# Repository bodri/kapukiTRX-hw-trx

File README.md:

# Redundant RC transmitter module & 8 channel receiver
RC Receiver and transmitter module using redundant SX1280 RF modules.

The [firmware](https://github.com/bodri/kapukiTRX-fw-trx) is still under development, but you can take a look already...

[Please take a look at my previous project here](https://github.com/bodri/RcReceiver)

# Design

# Manufacturing
I would like to compare services from [OSHPark](http://oshpark.com)/[OSH Stencils](https://www.oshstencils.com) and [JLCPCB](http://jlcpcb.com), so I ordered:

| Manufacturer | Items             | Price  | Order date | Shipped      | Received   | Total days |
|--------------|-------------------|--------|------------|--------------|------------|------------|
| OSHPark      | 3 PCBs            | $19.80 | 09/11/2019 | 21/11/2019** | 17/12/2019 | 21 (35)**  |
| OSH Stencils | 1 stencil         | $21.60 | 09/11/2019 | 12/11/2019   | 19/11/2019 | 10         |
| JLCPCB       | 10 PCBs + stencil | $28.33 | 09/11/2019 | 14/11/2019   | 03/12/2019 | 21         |

<sub>** Originally was shipped on 21/11/2019 and received on the same day as the JLCPCB package, but I have received a message that the PCBs have "Severe over-etching in some regions" therefore not to use them. OSHPark refabricated them and I received the second batch on 17/12/2019.<sub>

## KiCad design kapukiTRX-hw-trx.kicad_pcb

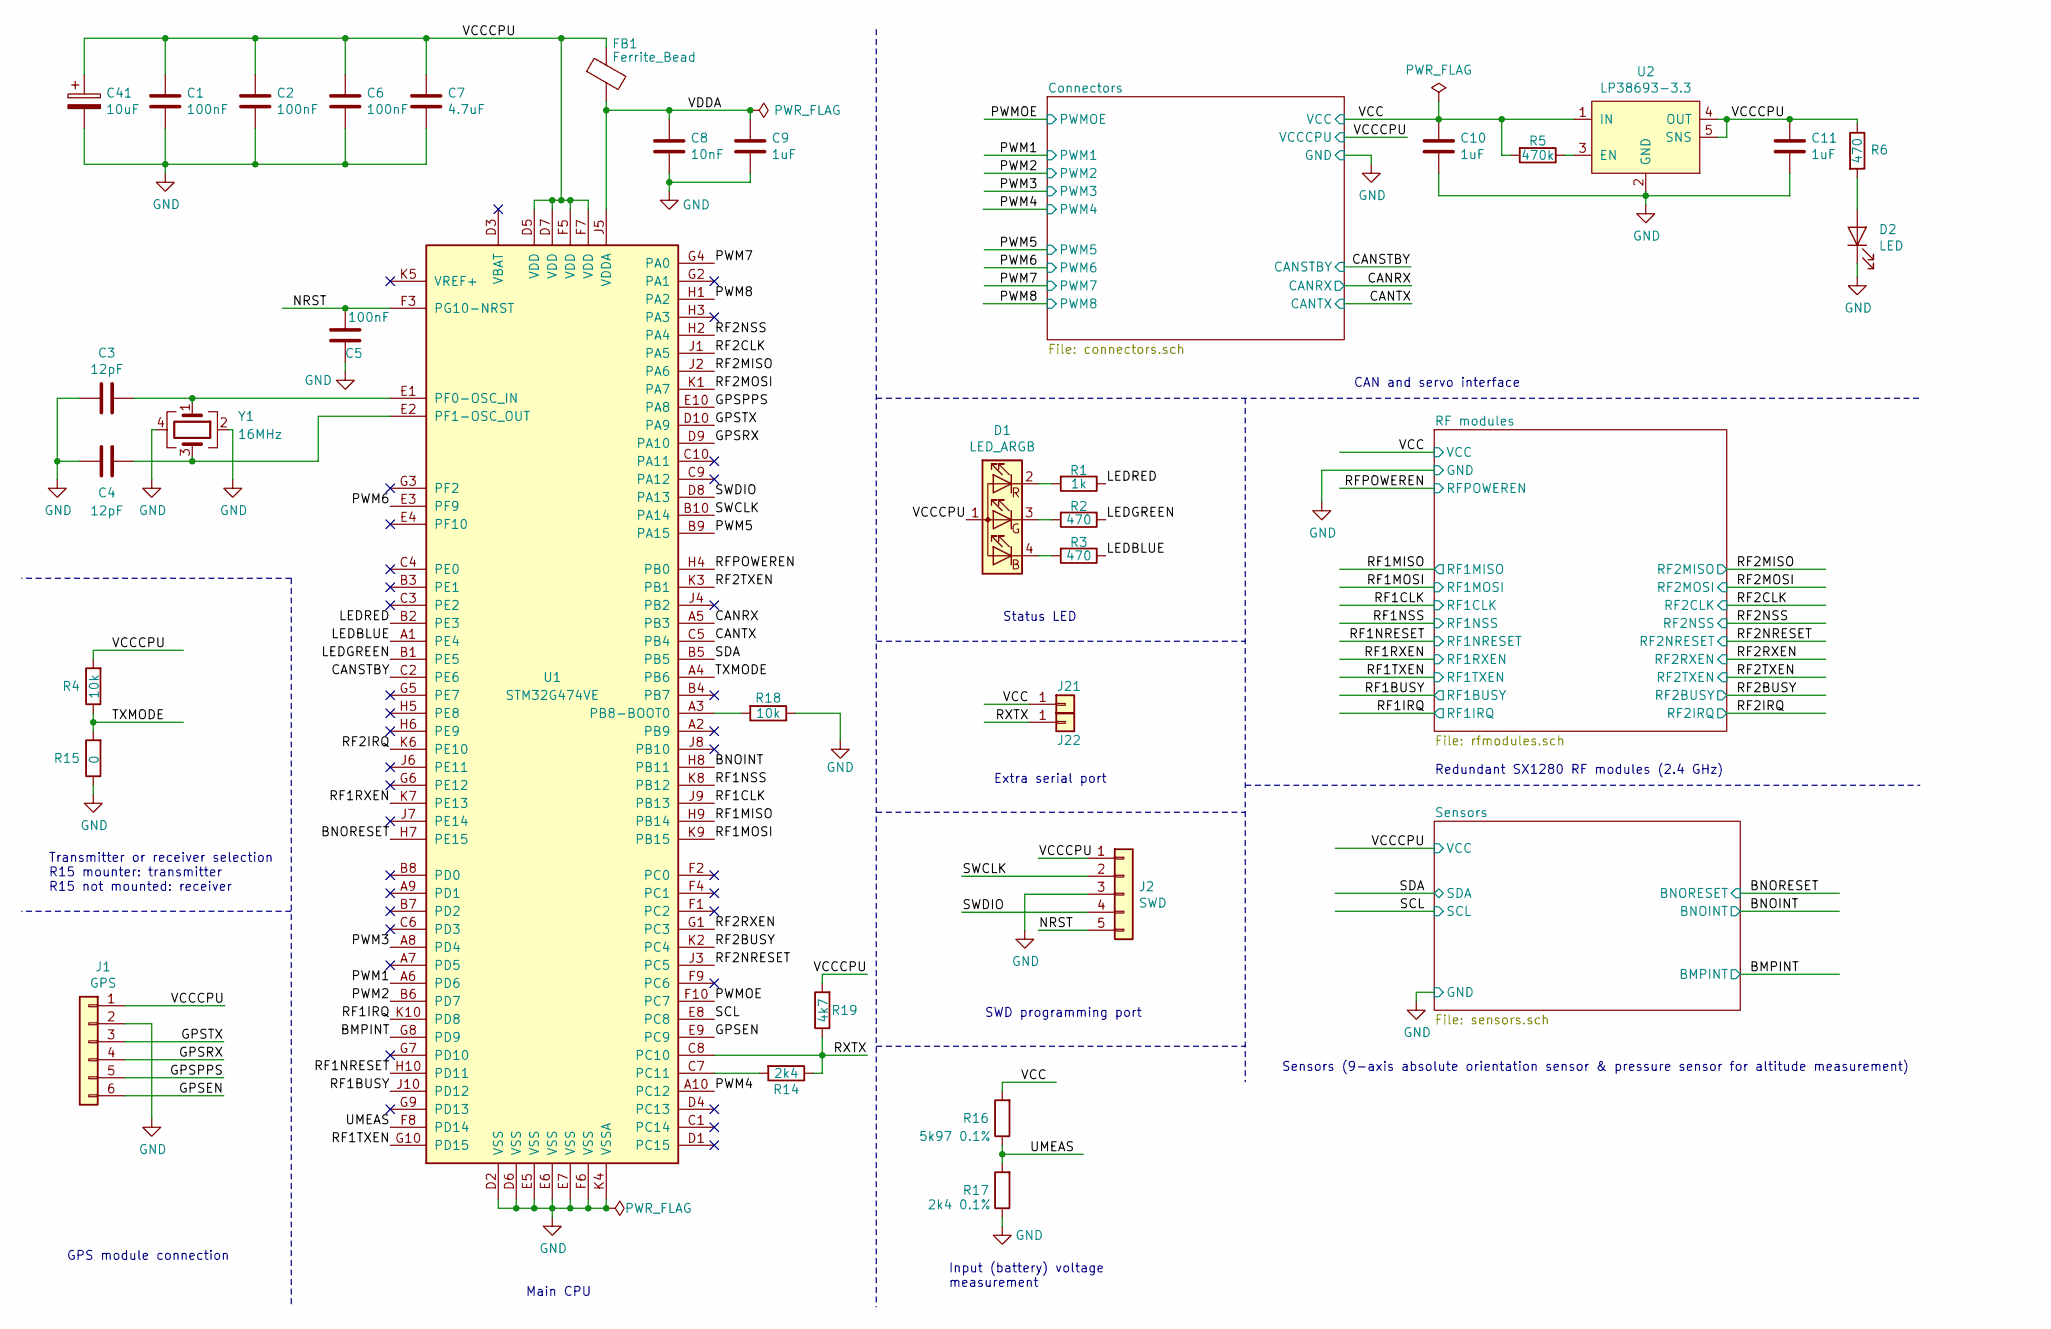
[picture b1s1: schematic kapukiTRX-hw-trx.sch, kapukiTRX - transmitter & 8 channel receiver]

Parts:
C1, C2, C5, C6: 100nF; C_0402_1005Metric
C3, C4: 12pF; C_0402_1005Metric
C7: 4.7uF; C_0402_1005Metric
C8: 10nF; C_0402_1005Metric
C9, C10, C11: 1uF; C_0402_1005Metric
C41: 10uF; CP_EIA-3216-18_Kemet-A
D1: LED_ARGB; LED_Lumex-LX0404
D2: LED; LED_0402_1005Metric
FB1: Ferrite_Bead; L_0402_1005Metric
J1: GPS; JST_SH_BM06B-SRSS-TB_1x06-1MP_P1.00mm_Vertical
J2: SWD; JST_SH_BM05B-SRSS-TB_1x05-1MP_P1.00mm_Vertical
J21, J22: Conn_01x01; PinHeader_1x01_P1.27mm
R1: 1k; R_0402_1005Metric
R2, R3, R6: 470; R_0402_1005Metric
R4, R18: 10k; R_0402_1005Metric
R5: 470k; R_0402_1005Metric
R14: 2k4; R_0402_1005Metric
R15: 0; R_0402_1005Metric
R16: 5k97 0.1%; R_0402_1005Metric
R17: 2k4 0.1%; R_0402_1005Metric
R19: 4k7; R_0402_1005Metric
U1: STM32G474VE; TFBGA-100_10x10_8.0x8.0mm
U2: LP38693-3.3; WSON-6_3x3mm_Pitch0.95mm
Y1: 16MHz; Oscillator_SMD_SeikoEpson_SG210-4Pin_2.5x2.0mm

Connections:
/BMPINT: U1.G8 (PD9); also elsewhere on the board
/BNOINT: U1.H8 (PB11); also elsewhere on the board
/BNORESET: U1.H7 (PE15); also elsewhere on the board
/CANRX: U1.A5 (PB3); also elsewhere on the board
/CANSTBY: U1.C2 (PE6); also elsewhere on the board
/CANTX: U1.C5 (PB4); also elsewhere on the board
/GPSEN: J1.6, U1.E9 (PC9)
/GPSPPS: J1.5, U1.E10 (PA8)
/GPSRX: J1.4, U1.D9 (PA10)
/GPSTX: J1.3, U1.D10 (PA9)
/LEDBLUE: R3.1, U1.A1 (PE4)
/LEDGREEN: R2.1, U1.B1 (PE5)
/LEDRED: R1.1, U1.B2 (PE3)
/NRST: C5.2, J2.5, U1.F3 (PG10-NRST)
/PWM1: U1.A6 (PD6); also elsewhere on the board
/PWM2: U1.B6 (PD7); also elsewhere on the board
/PWM3: U1.A8 (PD4); also elsewhere on the board
/PWM4: U1.A10 (PC12); also elsewhere on the board
/PWM5: U1.B9 (PA15); also elsewhere on the board
/PWM6: U1.E3 (PF9); also elsewhere on the board
/PWM7: U1.G4 (PA0); also elsewhere on the board
/PWM8: U1.H1 (PA2); also elsewhere on the board
/PWMOE: U1.F10 (PC7); also elsewhere on the board
/RF1BUSY: U1.J10 (PD12); also elsewhere on the board
/RF1CLK: U1.J9 (PB13); also elsewhere on the board
/RF1IRQ: U1.K10 (PD8); also elsewhere on the board
/RF1MISO: U1.H9 (PB14); also elsewhere on the board
/RF1MOSI: U1.K9 (PB15); also elsewhere on the board
/RF1NRESET: U1.H10 (PD11); also elsewhere on the board
/RF1NSS: U1.K8 (PB12); also elsewhere on the board
/RF1RXEN: U1.K7 (PE13); also elsewhere on the board
/RF1TXEN: U1.G10 (PD15); also elsewhere on the board
/RF2BUSY: U1.K2 (PC4); also elsewhere on the board
/RF2CLK: U1.J1 (PA5); also elsewhere on the board
/RF2IRQ: U1.K6 (PE10); also elsewhere on the board
/RF2MISO: U1.J2 (PA6); also elsewhere on the board
/RF2MOSI: U1.K1 (PA7); also elsewhere on the board
/RF2NRESET: U1.J3 (PC5); also elsewhere on the board
/RF2NSS: U1.H2 (PA4); also elsewhere on the board
/RF2RXEN: U1.G1 (PC3); also elsewhere on the board
/RF2TXEN: U1.K3 (PB1); also elsewhere on the board
/RFPOWEREN: U1.H4 (PB0); also elsewhere on the board
/RXTX: J22.1, R14.1, R19.1, U1.C8 (PC10)
/SCL: U1.E8 (PC8); also elsewhere on the board
/SDA: U1.B5; also elsewhere on the board
/SWCLK: J2.2, U1.B10 (PA14)
/SWDIO: J2.4, U1.D8 (PA13)
/TXMODE: R4.1, R15.2, U1.A4 (PB6)
/UMEAS: R16.1, R17.2, U1.F8 (PD14)
/VCCCPU: C1.1, C2.1, C6.1, C7.1, C11.1, C41.1, D1.1 (A), FB1.1, J1.1, J2.1, R4.2, R6.1, R19.2, U1.D5 (VDD), U1.D7 (VDD), U1.F5 (VDD), U1.F7 (VDD), U2.4 (OUT), U2.5 (SNS); also elsewhere on the board
/VDDA: C8.1, C9.1, FB1.2, U1.J5 (VDDA)
GND: C1.2, C2.2, C3.2, C4.2, C5.1, C6.2, C7.2, C8.2, C9.2, C10.2, C11.2, C41.2, D2.1 (K), J1.2, J2.3, R15.1, R17.1, R18.1, U1.D2 (VSS), U1.D6 (VSS), U1.E5 (VSS), U1.E6 (VSS), U1.E7 (VSS), U1.F6 (VSS), U1.K4 (VSSA), U2.2 (GND), U2.7 (GND), Y1.2, Y1.4; also elsewhere on the board
IN: C10.1, J21.1, R5.2, R16.2, U2.1 (IN), U2.6 (IN); also elsewhere on the board
unnamed: C3.1, U1.E1 (PF0-OSC_IN), Y1.1
unnamed: C4.1, U1.E2 (PF1-OSC_OUT), Y1.3
unnamed: D1.2 (RK), R1.2
unnamed: D1.3 (GK), R2.2
unnamed: D1.4 (BK), R3.2
unnamed: D2.2 (A), R6.2
unnamed: R5.1, U2.3 (EN)
unnamed: R14.2, U1.C7 (PC11)
unnamed: R18.2, U1.A3 (PB8-BOOT0)

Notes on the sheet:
Status LED
Extra serial port
SWD programming port
Redundant SX1280 RF modules (2.4 GHz)
Sensors (9-axis absolute orientation sensor & pressure sensor for altitude measurement)
Transmitter or receiver selection R15 mounter: transmitter R15 not mounted: receiver
GPS module connection
CAN and servo interface
Main CPU
Input (battery) voltage measurement

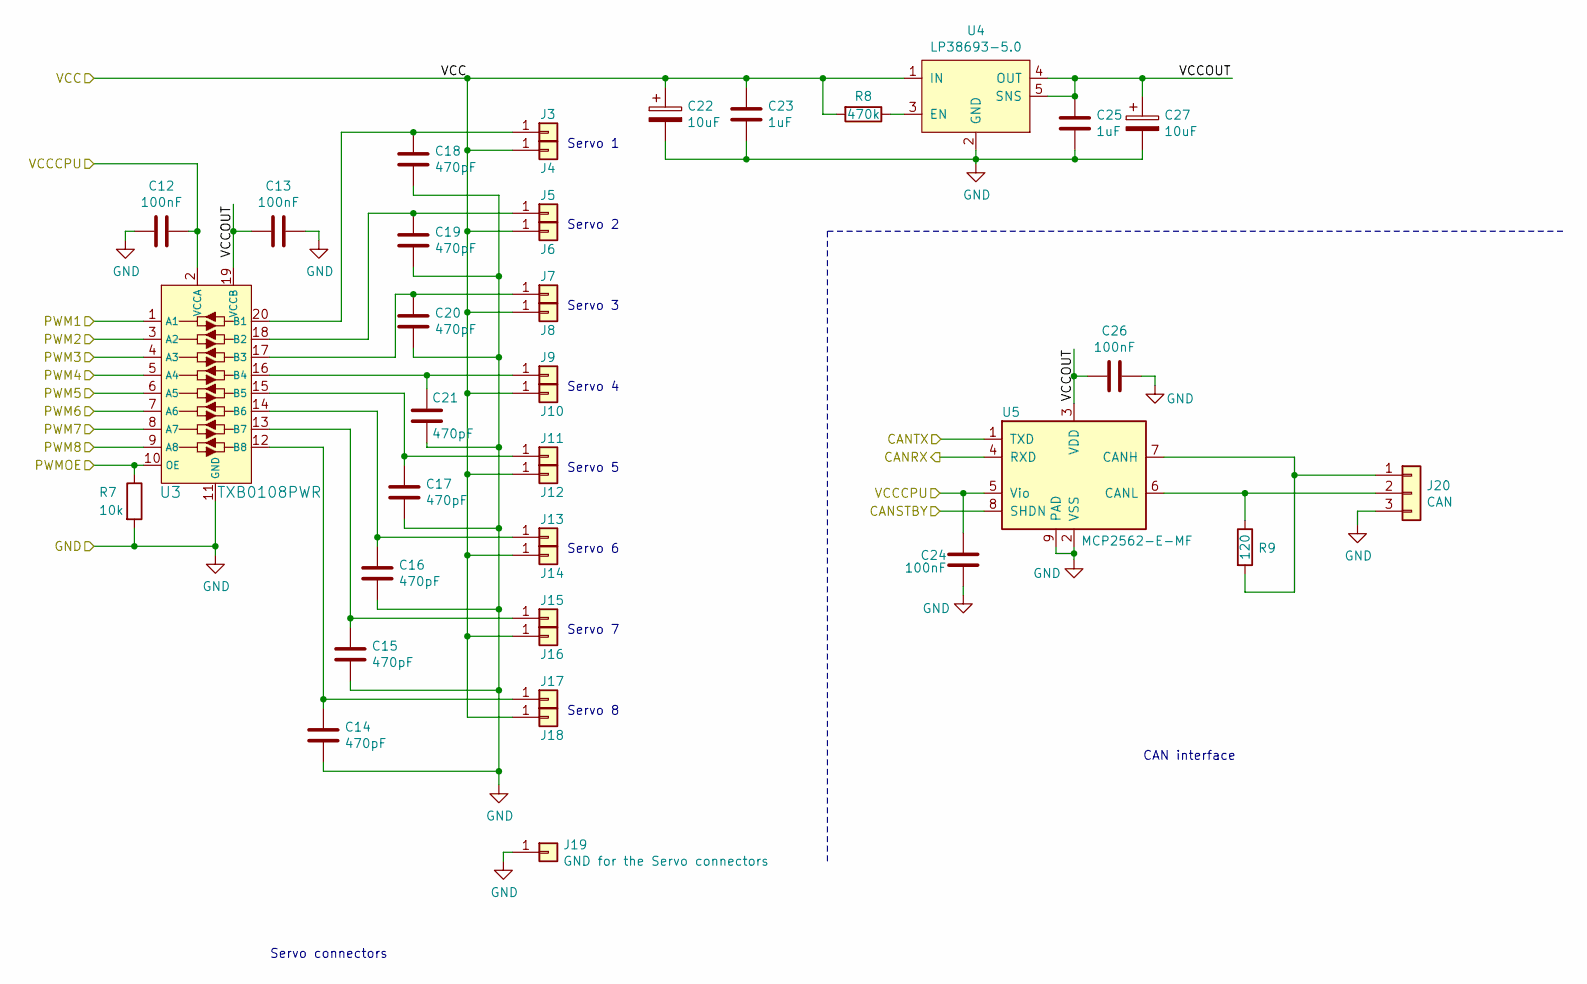
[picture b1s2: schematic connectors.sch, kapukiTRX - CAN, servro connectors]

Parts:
C12, C13, C24, C26: 100nF; C_0402_1005Metric
C14, C15, C16, C17, C18, C19, C20, C21: 470pF; C_0402_1005Metric
C22, C27: 10uF; CP_EIA-3216-18_Kemet-A
C23, C25: 1uF; C_0402_1005Metric
J3, J4, J5, J6, J7, J8, J9, J10, J11, J12, J13, J14, J15, J16, J17, J18: Conn_01x01; PinHeader_1x01_P1.27mm
J19: GND for the Servo connectors; PinHeader_1x01_P2.54mm_Vertical
J20: CAN; JST_SH_BM03B-SRSS-TB_1x03-1MP_P1.00mm_Vertical
R7: 10k; R_0402_1005Metric
R8: 470k; R_0402_1005Metric
R9: 120; R_0402_1005Metric
U3: TXB0108PWR; TSSOP-20_W4.4mm; MPN TXB0108PWR; Digi-Key_PN 296-21527-1-ND
U4: LP38693-5.0; WSON-6_3x3mm_Pitch0.95mm
U5: MCP2562-E-MF; DFN-8-1EP_3x3mm_P0.65mm_EP1.55x2.4mm

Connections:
/CANRX: U5.4 (RXD); also elsewhere on the board
/CANSTBY: U5.8 (SHDN); also elsewhere on the board
/CANTX: U5.1 (TXD); also elsewhere on the board
/Connectors/VCCOUT: C13.2, C25.1, C26.2, C27.1, U3.19 (VCCB), U4.4 (OUT), U4.5 (SNS), U5.3 (VDD)
/PWM1: U3.1 (A1); also elsewhere on the board
/PWM2: U3.3 (A2); also elsewhere on the board
/PWM3: U3.4 (A3); also elsewhere on the board
/PWM4: U3.5 (A4); also elsewhere on the board
/PWM5: U3.6 (A5); also elsewhere on the board
/PWM6: U3.7 (A6); also elsewhere on the board
/PWM7: U3.8 (A7); also elsewhere on the board
/PWM8: U3.9 (A8); also elsewhere on the board
/PWMOE: R7.1, U3.10 (OE); also elsewhere on the board
/VCCCPU: C12.1, C24.2, U3.2 (VCCA), U5.5 (Vio); also elsewhere on the board
GND: C12.2, C13.1, C14.2, C15.2, C16.2, C17.2, C18.2, C19.2, C20.2, C21.2, C22.2, C23.2, C24.1, C25.2, C26.1, C27.2, J19.1, J20.3, R7.2, U3.11 (GND), U4.2 (GND), U4.7 (GND), U5.2 (VSS), U5.9 (PAD); also elsewhere on the board
IN: C22.1, C23.1, J4.1, J6.1, J8.1, J10.1, J12.1, J14.1, J16.1, J18.1, R8.2, U4.1 (IN), U4.6 (IN); also elsewhere on the board
unnamed: C14.1, J17.1, U3.12 (B8)
unnamed: C15.1, J15.1, U3.13 (B7)
unnamed: C16.1, J13.1, U3.14 (B6)
unnamed: C17.1, J11.1, U3.15 (B5)
unnamed: C18.1, J3.1, U3.20 (B1)
unnamed: C19.1, J5.1, U3.18 (B2)
unnamed: C20.1, J7.1, U3.17 (B3)
unnamed: C21.1, J9.1, U3.16 (B4)
unnamed: J20.1, R9.2, U5.7 (CANH)
unnamed: J20.2, R9.1, U5.6 (CANL)
unnamed: R8.1, U4.3 (EN)

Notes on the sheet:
Servo 1
Servo 2
Servo 3
Servo 4
Servo 5
Servo 6
Servo 7
Servo 8
CAN interface
Servo connectors

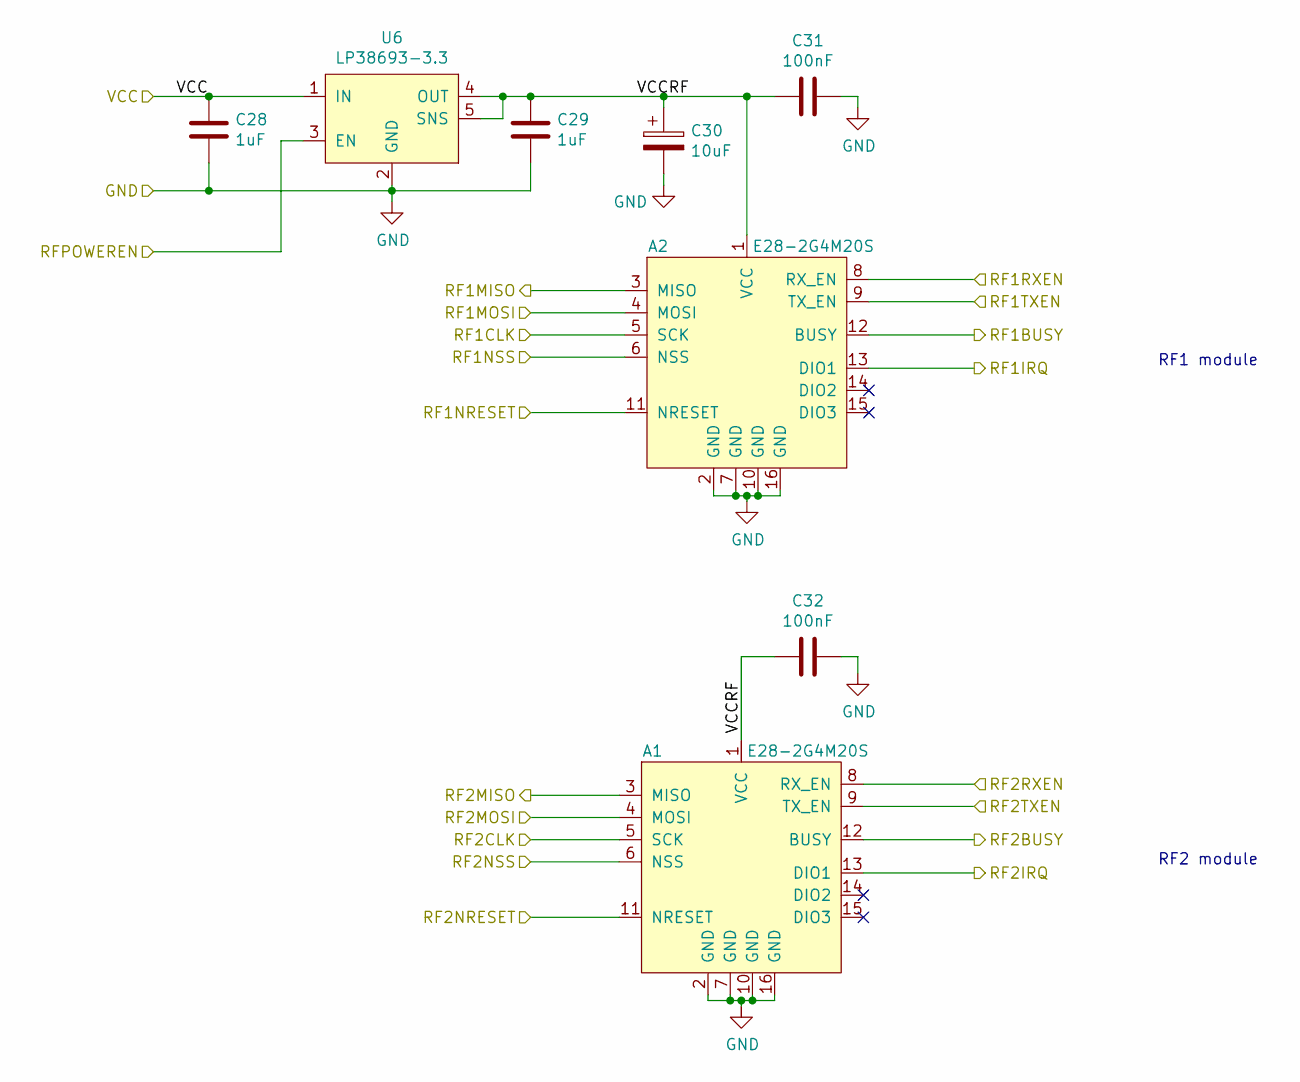
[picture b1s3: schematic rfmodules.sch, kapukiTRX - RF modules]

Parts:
A1, A2: E28-2G4M20S
C28, C29: 1uF; C_0402_1005Metric
C30: 10uF; CP_EIA-3216-18_Kemet-A
C31, C32: 100nF; C_0402_1005Metric
U6: LP38693-3.3; WSON-6_3x3mm_Pitch0.95mm

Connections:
/RF1BUSY: A2.12 (BUSY); also elsewhere on the board
/RF1CLK: A2.5 (SCK); also elsewhere on the board
/RF1IRQ: A2.13 (DIO1); also elsewhere on the board
/RF1MISO: A2.3 (MISO); also elsewhere on the board
/RF1MOSI: A2.4 (MOSI); also elsewhere on the board
/RF1NRESET: A2.11 (NRESET); also elsewhere on the board
/RF1NSS: A2.6 (NSS); also elsewhere on the board
/RF1RXEN: A2.8 (RX_EN); also elsewhere on the board
/RF1TXEN: A2.9 (TX_EN); also elsewhere on the board
/RF2BUSY: A1.12 (BUSY); also elsewhere on the board
/RF2CLK: A1.5 (SCK); also elsewhere on the board
/RF2IRQ: A1.13 (DIO1); also elsewhere on the board
/RF2MISO: A1.3 (MISO); also elsewhere on the board
/RF2MOSI: A1.4 (MOSI); also elsewhere on the board
/RF2NRESET: A1.11 (NRESET); also elsewhere on the board
/RF2NSS: A1.6 (NSS); also elsewhere on the board
/RF2RXEN: A1.8 (RX_EN); also elsewhere on the board
/RF2TXEN: A1.9 (TX_EN); also elsewhere on the board
/RF modules/VCCRF: A1.1 (VCC), A2.1 (VCC), C29.1, C30.1, C31.2, C32.2, U6.4 (OUT), U6.5 (SNS)
/RFPOWEREN: U6.3 (EN); also elsewhere on the board
GND: A1.2 (GND), A1.7 (GND), A1.10 (GND), A1.16 (GND), A2.2 (GND), A2.7 (GND), A2.10 (GND), A2.16 (GND), C28.2, C29.2, C30.2, C31.1, C32.1, U6.2 (GND), U6.7 (GND); also elsewhere on the board
IN: C28.1, U6.1 (IN), U6.6 (IN); also elsewhere on the board

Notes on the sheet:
RF1 module
RF2 module

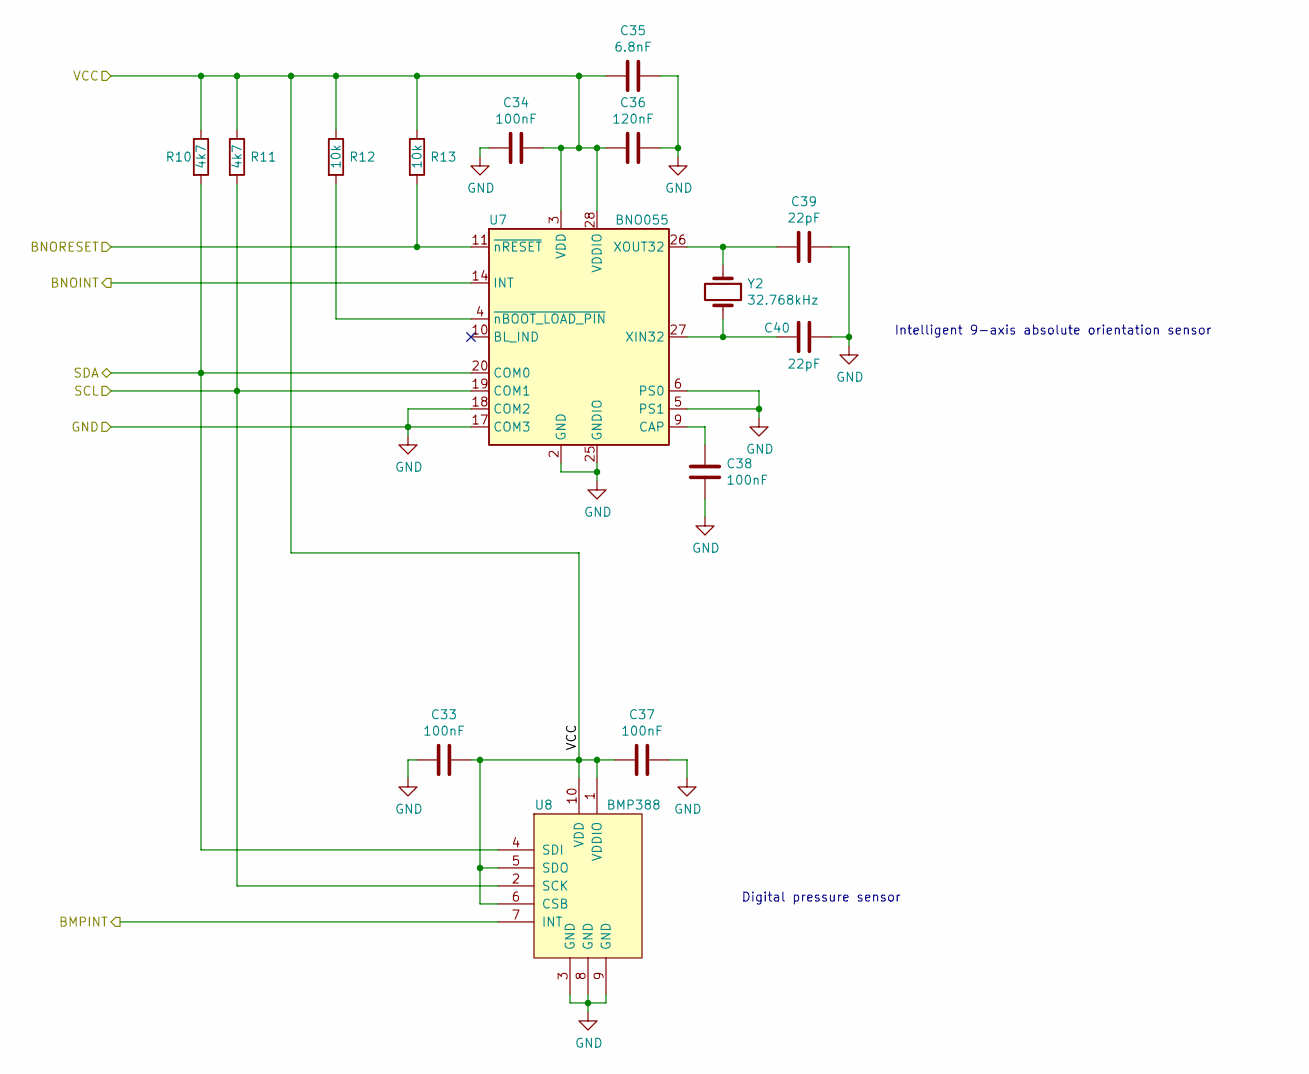
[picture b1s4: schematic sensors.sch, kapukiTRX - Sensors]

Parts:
C33, C34, C37, C38: 100nF; C_0402_1005Metric
C35: 6.8nF; C_0402_1005Metric
C36: 120nF; C_0402_1005Metric
C39, C40: 22pF; C_0402_1005Metric
R10, R11: 4k7; R_0402_1005Metric
R12, R13: 10k; R_0402_1005Metric
U7: BNO055; LGA-28_5.2x3.8mm_P0.5mm
U8: BMP388; Bosch_LGA10_2x2mm_Pitch0.5mm
Y2: 32.768kHz; Crystal_SMD_2012-2Pin_2.0x1.2mm

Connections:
/BMPINT: U8.7 (INT); also elsewhere on the board
/BNOINT: U7.14 (INT); also elsewhere on the board
/BNORESET: R13.2, U7.11 (~nRESET); also elsewhere on the board
/SCL: R11.2, U7.19 (COM1), U8.2 (SCK); also elsewhere on the board
/SDA: R10.2, U7.20 (COM0), U8.4 (SDI); also elsewhere on the board
/VCCCPU: C33.1, C34.1, C35.2, C36.2, C37.2, R10.1, R11.1, R12.1, R13.1, U7.3 (VDD), U7.28 (VDDIO), U8.1 (VDDIO), U8.5 (SDO), U8.6 (CSB), U8.10 (VDD); also elsewhere on the board
GND: C33.2, C34.2, C35.1, C36.1, C37.1, C38.2, C39.1, C40.1, U7.2 (GND), U7.5 (PS1), U7.6 (PS0), U7.15 (GNDIO), U7.16 (GNDIO), U7.17 (COM3), U7.18 (COM2), U7.25 (GNDIO), U8.3 (GND), U8.8 (GND), U8.9 (GND); also elsewhere on the board
unnamed: C38.1, U7.9 (CAP)
unnamed: C39.2, U7.26 (XOUT32), Y2.1
unnamed: C40.2, U7.27 (XIN32), Y2.2
unnamed: R12.2, U7.4 (~nBOOT_LOAD_PIN)

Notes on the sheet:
Digital pressure sensor
Intelligent 9-axis absolute orientation sensor

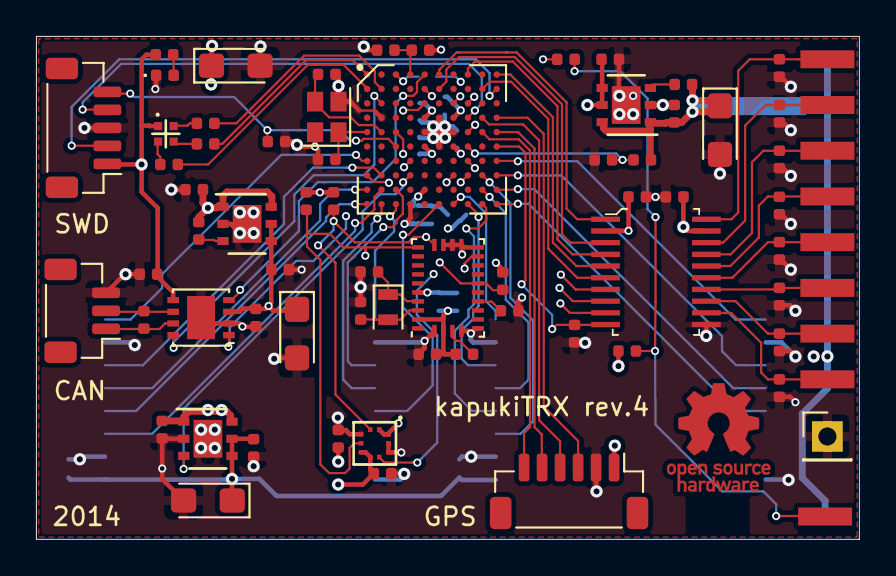
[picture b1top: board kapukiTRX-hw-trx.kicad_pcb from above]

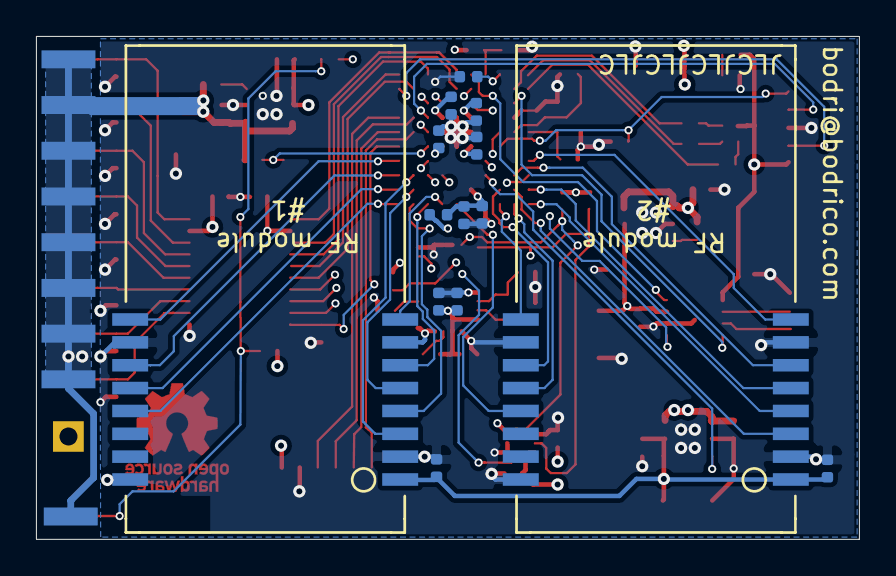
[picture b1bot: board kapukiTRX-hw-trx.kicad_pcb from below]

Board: 4 copper layers, 45.7 x 27.9 mm, 97 parts (23 on the bottom side), 79 nets.

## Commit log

2019-10-27 Add missing files
2019-10-27 Use it on mac
2019-10-27 Revert "Use it on mac"
    This reverts commit 31182a4bd36aa13d038d509ee2b2cd4b0d770585.
2019-10-27 Add git ignore file
2019-10-29 Add sensors (altitude/9 axis orientation)
2019-10-29 Wiring sensors
2019-10-29 Use crystal with smaller footprint
2019-10-31 Change processor to G4 series
2019-11-02 Placing components and start routing
2019-11-05 Add nets more nets
2019-11-05 Change some pins for better routing
2019-11-08 Add proper footprint for BMP388
2019-11-08 Small changes
2019-11-08 Make sure that wires underneath the BGA goes middle between pins
2019-11-08 Swap pwm lines for better routing
2019-11-08 Almost finish routing
2019-11-08 Finish routing
2019-11-09 Add support for EX bus
2019-11-09 Routing for EX bus
2019-11-09 Change name of sheets
2019-11-09 Add an elec cap to cup rail
2019-11-09 Add Open hardware logo
2019-11-09 Final version
2019-11-10 Add 3D view
2019-11-10 Add README
2019-11-10 Better project description
2019-11-10 Add schematic.pdf
2019-11-15 Fix connector placing
2019-11-19 Add manufacturing dates
2019-11-22 PCB shipped from OSHPark
2019-11-22 Better wording
2019-12-03 PCBs have been landed
2019-12-19 PCBs are received from OSHPark
2020-01-01 Fix BMP388 footprint issue
2020-01-03 Final changes for rev.3
2020-03-29 Add boot resistor, and fix CAN RX pin
2020-03-29 Add pull-up for uart
2020-03-30 rev.4 sent to JLCPCB
2020-03-31 Upload rev.4 3D image
2020-04-24 Add interactive bom
2020-04-24 Make some value changes for consistency
2020-04-24 Remove R18 from silk
2020-04-24 Add OSH logo and update schematic.pdf
2020-05-07 Add license
